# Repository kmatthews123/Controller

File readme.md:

# Custom ROV Controller

###### What is this project?

I designed this controller as a combination of work project and learning tool

The original genesis of this project was a whacky controller thought up during many long hours of driving with myself and a co-worker. I decided to build a custom ROV controller based on a guitar hero controller for laughs. The controller was a lot easier to build than I thought it would be and it was a very fun thing at my work Christmas party. 

The Guitar hero controller utilized all the buttons used by default on the guitar, I had to add a linear Potentiometer for the vertical propellor as well as the "whammy bar" as a self centering vertical propellor controller. I also added the joystick to the guitar. This was a fun project and while I did learn some stuff about circuit python I defiantly did not plan to use this for more than a gag.

#### The Real Controller

This controller was designed for use with a video ray pro4 ROV as a more comfortable and normal user interface device.

 I work at a company that uses a pro4 to inspect submerged structures. I found that the default controller from Video Ray is really uncomfortable to use for a full day and its design made it difficult for me to use during complex movements and actions. The  original controller (seen below)  shows up as a USB game-pad to the laptop that is used to communicate with the ROV. This computer uses windows 10 and using the USB controller utility included in windows I was able to map out how the video ray controller button map is seen by the system. From what I understand the pro4 has two compatible controllers, the normal industrial controller that my company normally uses and also the Logitech Cordless RumblePad 2 which is an old controller. Apparently you can edit xml files to make other controllers work with the pro4 but as engineering support has ended for this bot, I was left with the options of editing xml files that could potentially make my pro4 console unusable if i did something wrong (not an option as this is a work machine), download software to  remap the controller using software (This option was unappealing because I found this kind of software to be really hit and miss for the functions that I needed to setup) or design my own custom controller. 

I learned to use KiCAD 7.0 to design the custom PCB for this project. I have dabbled with electronics and code for years and have made several custom breadboards but the step to making my own distinct PCB was really interesting. The community for KiCad was very beginner friendly, and once I started to understand the structure of the program and the workflow the process began to make a lot of sense. I did do two different versions of this board. with the first version I was manually routing traces between my components and I realized that that was going to take way too long and for this application it didn't make much sense so I ended up auto routing the rest of the project. This worked fine though I do think that there are definitely routing things I could have improved.

 I also did not know how PCB manufacturers price out boards based on the amount of area that each board will take up in the batching process. Because of these things I found that I could save a bunch of money by making two distinct boards with one being the primary controller and the other being used for the shoulder buttons. the shoulder button board breaks in half for each side of the controller and everything is "wired" up really simply. I think adding an I2C analog input expansion board would have been a useful addition for this board (more on that later). I used OSH Park ~ for my PCB manufacturer because it was super easy to upload my KiCAD files to get them manufactured and the quality seems to be very good of the received circuit boards.

For designing the body of the controller, I used an online CAD program called OnShape. I took a fairly simple approach to this and imported all the boards and as many components as i could find models for, then built an assembled circuit board in an assembly. From there I used dimensions of the board to layout the base of the controller, and designed the front plate as a piece used to hold the shoulder buttons. The shoulder buttons are admittedly a bit rough; I considered a bunch of different ways of designing the buttons and I think the method I used is ok if I had executed it a bit better. If I were to do a full redesign I would probably do something more similar to paddles instead of the straight push buttons I ended up with. Lastly I designed the face plate of the controller based off the PCB assembly I had built before. OnShape has a really neat feature that allows for referencing assemblies in a part design workflow. this was really handy for designing parts in reference to other more complicated items. 

.png)

.png)

.png)

The CAD for this project is available in the 3d Models folder for both .step files and .3mf files. To view, copy and mess around with my original cad models checkout the below OnShape link.

https://cad.onshape.com/documents/9419f7314355fc0529143749/w/7dd750f9077cb0f159653e8e/e/9448de140bcc603a1d0b7df0

###### The electronics used

- RP2040 Adafruit Feather board

- with generic joysticks bought on digikey (COM-09032),

-  10 generic push buttons (6mm button height),

-  4 electrolytic capacitors to smooth joystick motion (47 Farad) 

- 1 10k linear POT. 

- an assortment of DuPont headers

###### The code!

The code for this project relies heavily on an awesome library called 
joystick_XL for circuit python. if you want to build a project like this one a great starting point is this GitHub and associated documentation.

 [GitHub - fasteddy516/CircuitPython_JoystickXL: Turn a CircuitPython device into a joystick controller with lots of inputs.](https://github.com/fasteddy516/CircuitPython_JoystickXL) 

I also ended up using some logic to switch inputs from a joystick on the right side to the potentiometer in the middle of the controller. This switch is useful because I found that I wanted a self centering vertical thruster control. For the Pro4 this means that when you are not actively using the controller the vertical propellor will be off. We set the pro4 to be neutrally buoyant when in fresh water. If you want to use the vertical propellor when not actually touching the controller (very useful for certain actions, motions and when lifting on items during an inspection). 

For those unfamiliar with the somewhat complicated process of building a USB HID device this library and circuit python in general makes things really easy. I can see lots of use cases for this library with all manner of custom interface devices and I could see this project acting as a good starting point for anyone trying to do something similar.

If you have a pro4 or another Video Ray device, there are a few changes I would make before trying to replicate this project 1:1. I don't plan on doing that for myself, but please reach out if you want to make your own, as I wouldn't mind sharing thoughts on an improved v2.

###### Lessons Learned and things to improve

- I should have used a micro controller with one additional analog input pin. This would have added flexibility for modifying the controller config. I find that I want to use the left hand controller for vertical movement and also for yaw and using the right stick for going forward and back. The current controller doesn't have the Y axis on the left hand stick connected to anything currently because I had to have the set and forget vertical propellor as an option. I think next time I would use something more like the Adafruit Feather M4 Express as it would have enough digital pins and enough analog IO to get the job done. this micro controller is a bit more spendy and I could also see using the Adafruit Feather 32u4 as a cheaper alternative. Basically something with the same pinout and more analog pins while still having at least 12 digital pins onboard. 

- The shoulder buttons are not very good. I think I could have planned those better and I think that next time I would use something more like a standard keyboard switch for the shoulder buttons or something like a simple paddle that would push on the head of a simple button. 

- I would like to explore a wireless version of this device at some point but this is pretty far down my list of priorities.

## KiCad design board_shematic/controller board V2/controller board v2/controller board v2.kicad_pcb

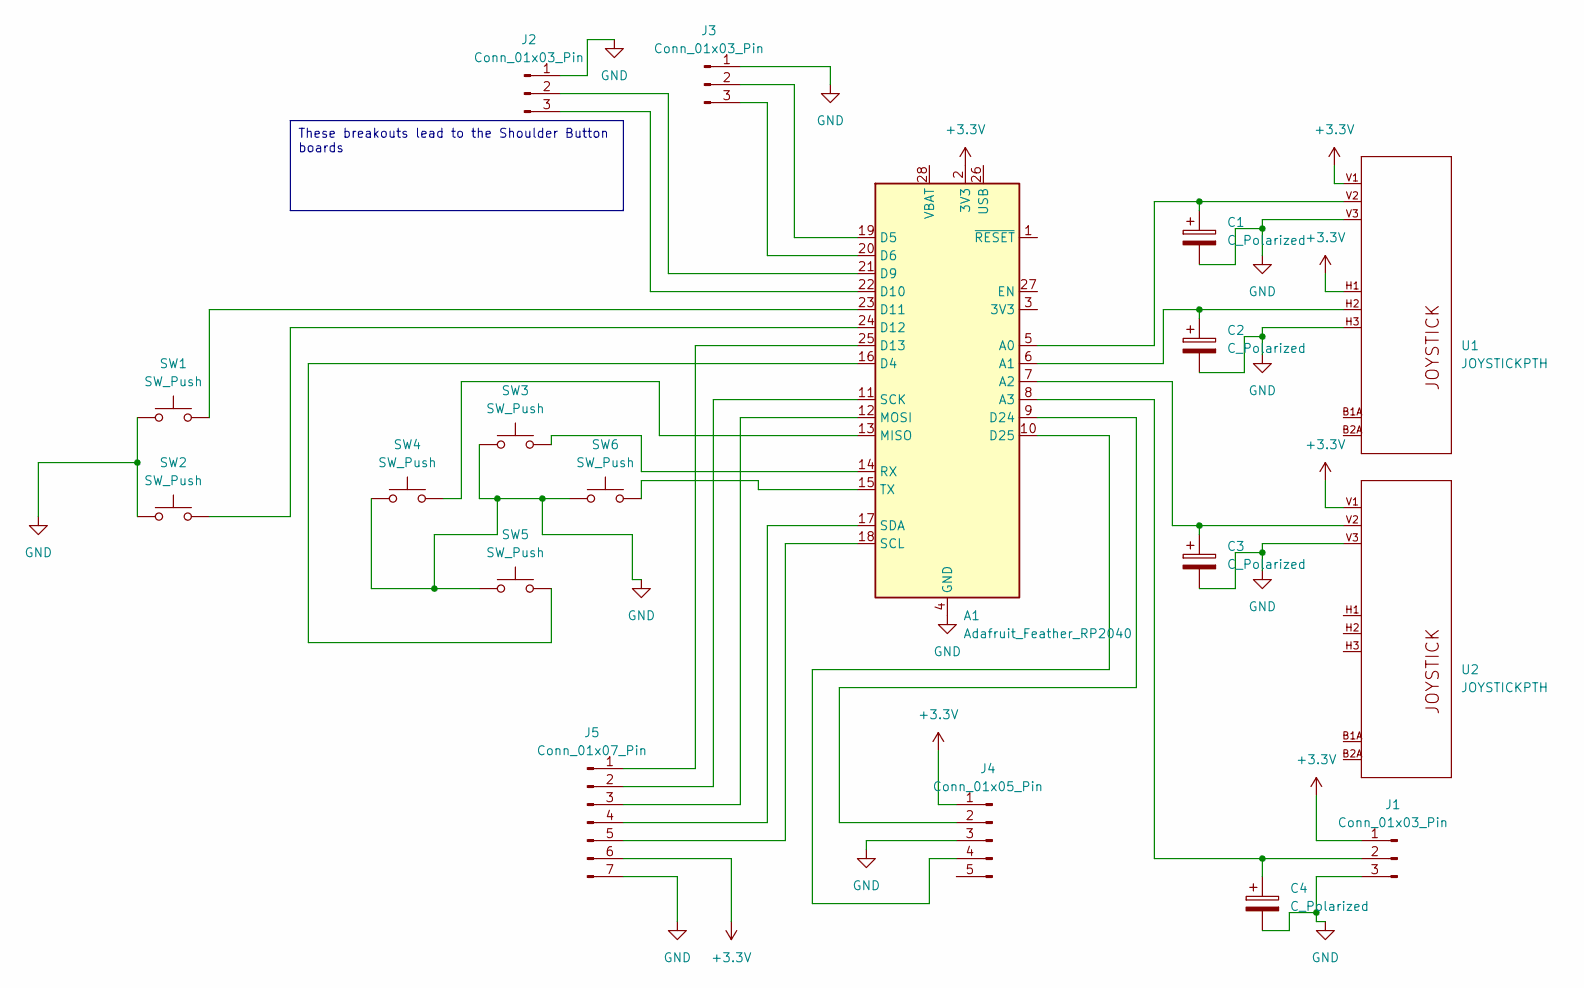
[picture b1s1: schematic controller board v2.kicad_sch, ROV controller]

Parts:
A1: Adafruit_Feather_RP2040; Adafruit_Feather
C1, C2, C3, C4: C_Polarized; CP_Radial_D5.0mm_P2.00mm
J1, J2, J3: Conn_01x03_Pin; PinHeader_1x03_P2.54mm_Vertical
J4: Conn_01x05_Pin; PinHeader_1x05_P2.54mm_Horizontal
J5: Conn_01x07_Pin; PinHeader_1x07_P2.54mm_Horizontal
SW1, SW2, SW3, SW4, SW5, SW6: SW_Push; SW_PUSH_6mm_H5mm
U1, U2: JOYSTICKPTH; XDCR_COM-09032

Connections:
+3.3V: A1.2 (3V3), J1.1, J4.1, J5.6, U1.H1 (H+), U1.V1 (V+), U2.V1 (V+)
GND: A1.4 (GND), C1.2, C2.2, C3.2, C4.2, J1.3, J2.1, J3.1, J4.3, J5.7, SW1.1, SW2.1, SW3.1, SW4.1, SW5.1, SW6.1, U1.H3 (H-), U1.V3 (V-), U2.V3 (V-)
unnamed: A1.5 (A0), C1.1, U1.V2 (V)
unnamed: A1.6 (A1), C2.1, U1.H2 (H)
unnamed: A1.7 (A2), C3.1, U2.V2 (V)
unnamed: A1.8 (A3), C4.1, J1.2
unnamed: A1.16 (D4), SW5.2
unnamed: A1.19 (D5), J3.2
unnamed: A1.20 (D6), J3.3
unnamed: A1.21 (D9), J2.2
unnamed: A1.22 (D10), J2.3
unnamed: A1.23 (D11), SW1.2
unnamed: A1.24 (D12), SW2.2
unnamed: A1.25 (D13), J5.1
unnamed: A1.9 (D24), J4.2
unnamed: A1.10 (D25), J4.4
unnamed: A1.13 (MISO), SW4.2
unnamed: A1.12 (MOSI), J5.3
unnamed: A1.14 (RX), SW3.2
unnamed: A1.11 (SCK), J5.2
unnamed: A1.18 (SCL), J5.5
unnamed: A1.17 (SDA), J5.4
unnamed: A1.15 (TX), SW6.2

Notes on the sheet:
These breakouts lead to the Shoulder Button boards

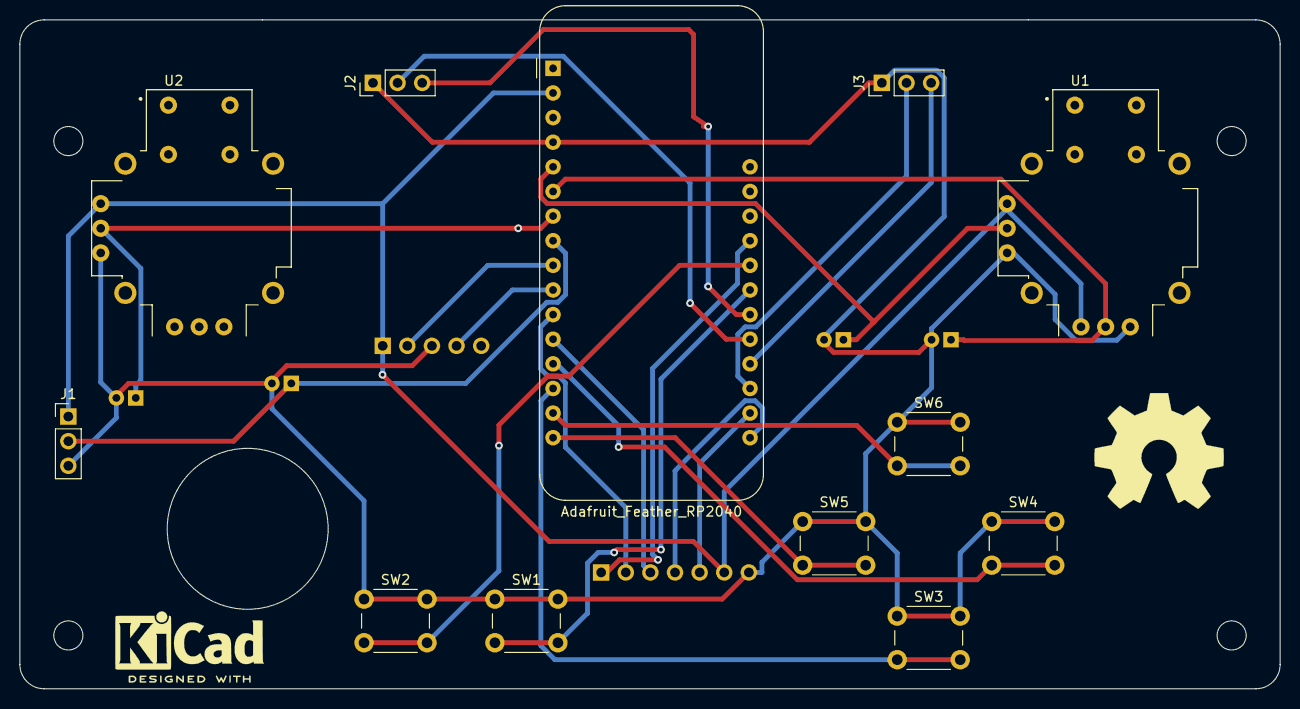
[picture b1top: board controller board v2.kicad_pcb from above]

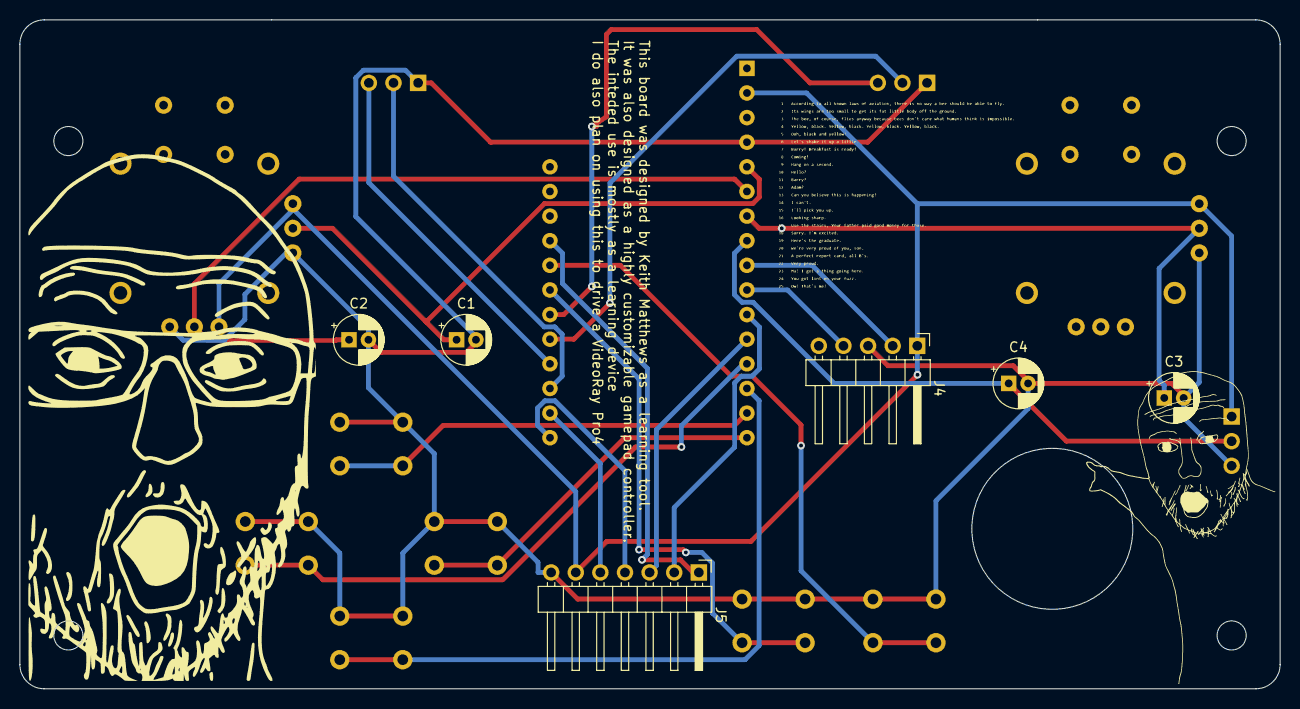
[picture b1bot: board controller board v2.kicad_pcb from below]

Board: 2 copper layers, 130.0 x 69.0 mm, 23 parts (9 on the bottom side), 23 nets.

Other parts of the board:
G34: LOGO; beemovie
G36: LOGO; Wojack1
G45: LOGO; Wojack2
REF15: OSHW-Symbol_13.4x12mm_SilkScreen
REF30: KiCad-Logo2_6mm_SilkScreen

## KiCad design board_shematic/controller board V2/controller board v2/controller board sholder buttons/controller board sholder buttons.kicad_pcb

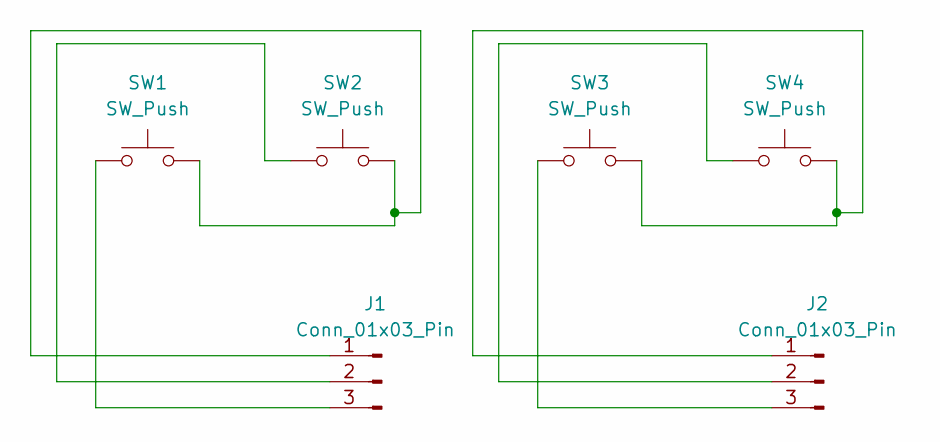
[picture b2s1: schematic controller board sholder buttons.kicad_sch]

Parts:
J1, J2: Conn_01x03_Pin; PinHeader_1x03_P2.54mm_Vertical
SW1, SW2, SW3, SW4: SW_Push; SW_PUSH_6mm_H5mm

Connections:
unnamed: J1.1, SW1.2, SW2.2
unnamed: J1.2, SW2.1
unnamed: J1.3, SW1.1
unnamed: J2.1, SW3.2, SW4.2
unnamed: J2.2, SW4.1
unnamed: J2.3, SW3.1

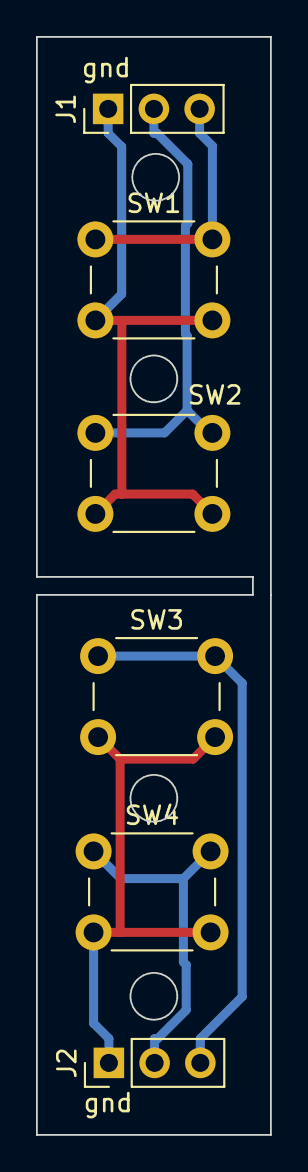
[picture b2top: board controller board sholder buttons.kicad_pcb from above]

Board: 2 copper layers, 13.0 x 61.0 mm, 6 parts (0 on the bottom side), 6 nets.

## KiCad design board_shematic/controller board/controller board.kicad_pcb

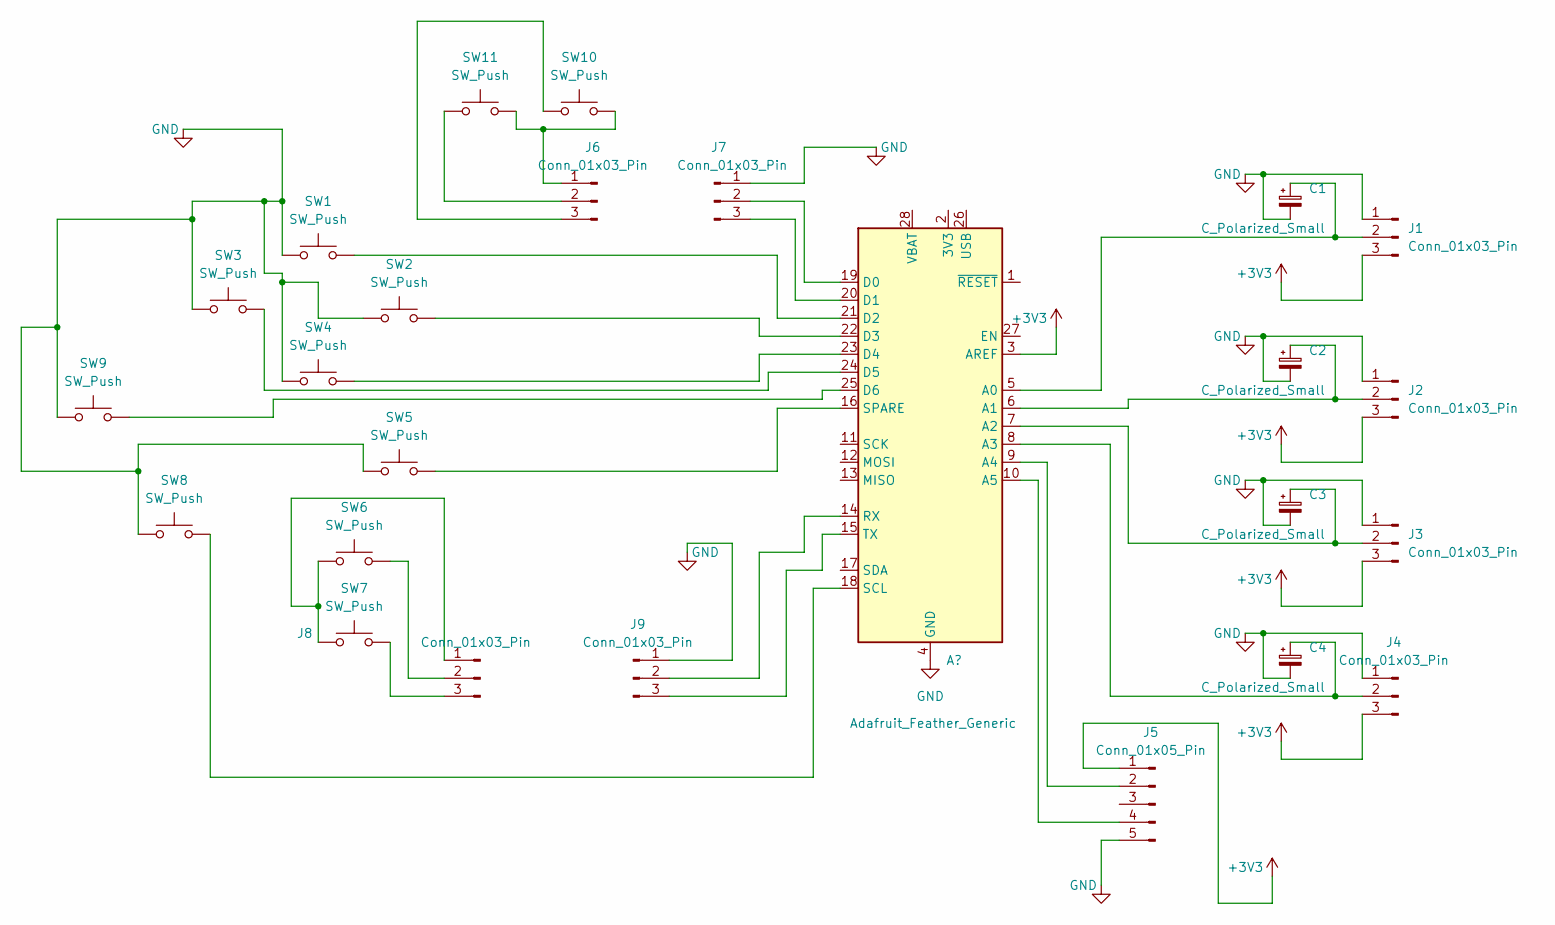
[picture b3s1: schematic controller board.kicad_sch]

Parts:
C1, C2, C3, C4: C_Polarized_Small; CP_Radial_D5.0mm_P2.00mm
J1, J2, J3, J4, J6, J7, J8, J9: Conn_01x03_Pin; PinHeader_1x03_P1.00mm_Vertical
J5: Conn_01x05_Pin; PinHeader_1x05_P1.00mm_Vertical
SW1, SW2, SW3, SW4, SW5, SW6, SW7, SW8, SW9, SW10, SW11: SW_Push; SW_SPST_SKQG_WithStem

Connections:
+3V3: J1.3, J2.3, J3.3, J4.3, J5.1; also elsewhere on the board
GND: C1.2, C2.2, C3.2, C4.2, J1.1, J2.1, J3.1, J4.1, J5.5, J7.1, J9.1, SW1.1, SW2.1, SW3.1, SW4.1, SW5.1, SW8.1, SW9.1; also elsewhere on the board
unnamed 2: C1.1, J1.2; also elsewhere on the board
unnamed 3: C2.1, J2.2; also elsewhere on the board
unnamed 4: C3.1, J3.2; also elsewhere on the board
unnamed 5: C4.1, J4.2; also elsewhere on the board
unnamed 6: SW5.2; also elsewhere on the board
unnamed 7: SW3.2; also elsewhere on the board
unnamed 8: SW9.2; also elsewhere on the board
unnamed 9: SW1.2; also elsewhere on the board
unnamed 10: SW2.2; also elsewhere on the board
unnamed 11: SW4.2; also elsewhere on the board
unnamed 12: J7.3; also elsewhere on the board
unnamed 13: J7.2; also elsewhere on the board
unnamed 14: J5.2; also elsewhere on the board
unnamed 15: J5.4; also elsewhere on the board
unnamed 16: J9.2; also elsewhere on the board
unnamed 17: SW8.2; also elsewhere on the board
unnamed 18: J9.3; also elsewhere on the board
unnamed: J6.1, SW10.2, SW11.2
unnamed: J6.2, SW11.1
unnamed: J6.3, SW10.1
unnamed: J8.1, SW6.1, SW7.1
unnamed: J8.2, SW6.2
unnamed: J8.3, SW7.2

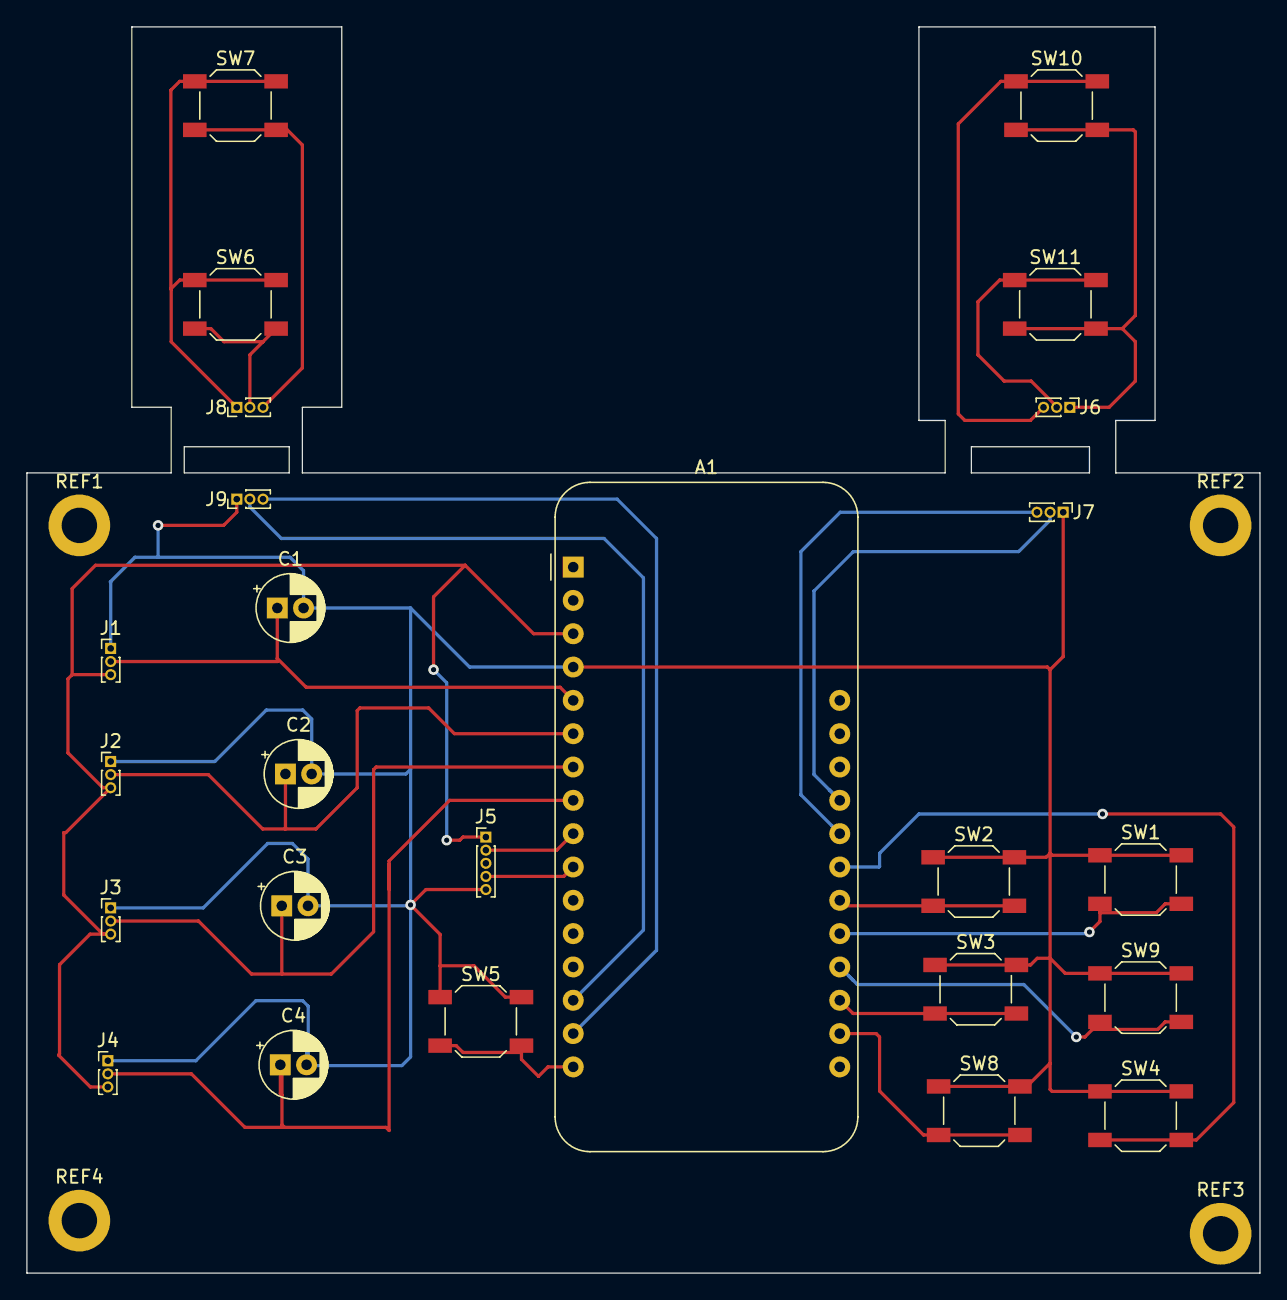
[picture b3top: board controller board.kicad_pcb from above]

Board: 2 copper layers, 94.0 x 95.0 mm, 29 parts (0 on the bottom side), 25 nets.

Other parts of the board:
A1: Adafruit_Feather_Generic; Adafruit_Feather
REF1, REF2, REF3, REF4: MountingHole_2.7mm_M2.5_DIN965_Pad

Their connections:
+3V3: A1.3 (3V3); also elsewhere on the board
GND: A1.4 (GND); also elsewhere on the board
unnamed 2: A1.5 (A0); also elsewhere on the board
unnamed 3: A1.6 (A1); also elsewhere on the board
unnamed 4: A1.7 (A2); also elsewhere on the board
unnamed 5: A1.8 (A3); also elsewhere on the board
unnamed 6: A1.16 (D4); also elsewhere on the board
unnamed 7: A1.19 (D5); also elsewhere on the board
unnamed 8: A1.20 (D6); also elsewhere on the board
unnamed 9: A1.21 (D9); also elsewhere on the board
unnamed 10: A1.22 (D10); also elsewhere on the board
unnamed 11: A1.23 (D11); also elsewhere on the board
unnamed 12: A1.24 (D12); also elsewhere on the board
unnamed 13: A1.25 (D13); also elsewhere on the board
unnamed 14: A1.9 (D24); also elsewhere on the board
unnamed 15: A1.10 (D25); also elsewhere on the board
unnamed 16: A1.14 (RX); also elsewhere on the board
unnamed 17: A1.18 (SCL); also elsewhere on the board
unnamed 18: A1.15 (TX); also elsewhere on the board

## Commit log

2024-01-11 Initial Commit of Controller Repo
2024-01-11 added readme
2024-01-11 updated controller items
2024-01-11 added gitignore
2024-01-11 removed unnessicary files for this project
2024-01-11 updated git ignore
2024-01-12 work on ensuring board is made correctly
2024-01-12 Updates to PCB design
2024-01-13 added credits file, added 3d model for 10k pot
2024-01-14 modified sholder buttons
2024-01-14 changed hole locations, updated pin orientation
2024-01-14 minor edits to pcb, end of night
2024-01-16 updated folder structure, removed un-needed stuff
2024-01-19 added 3d models of Controller
2024-01-21 3d models work
2024-02-18 added images and 3d model revisions
2024-02-18 added a bunch of images, CAD Changes
2024-02-18 cleaned up file structure, got rid of extra stuff
2024-02-18 Update readme.md
    struggling to get the markdown stuff
2024-02-21 Working on readme
2024-02-22 lots of updates to readme
2024-02-22 Minor proof-reading edits
